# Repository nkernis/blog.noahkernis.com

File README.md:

# blog.noahkernis.com

These are notes on writing posts. 

For usage, see [Hugo](https://gohugo.io/).

## Shortcodes

### Figure and Images

```go
{{< figure src="https://s3.amazonaws.com/media.noahkernis.com/images/life_is_weird.gif" alt="description of image" caption="[ title ]" >}}
```

### Code

```go
{{< code language="javascript" title="code code code" line-numbers="true">}}
function carl() {
	console.log("carla")
}
{{< /code >}}
```

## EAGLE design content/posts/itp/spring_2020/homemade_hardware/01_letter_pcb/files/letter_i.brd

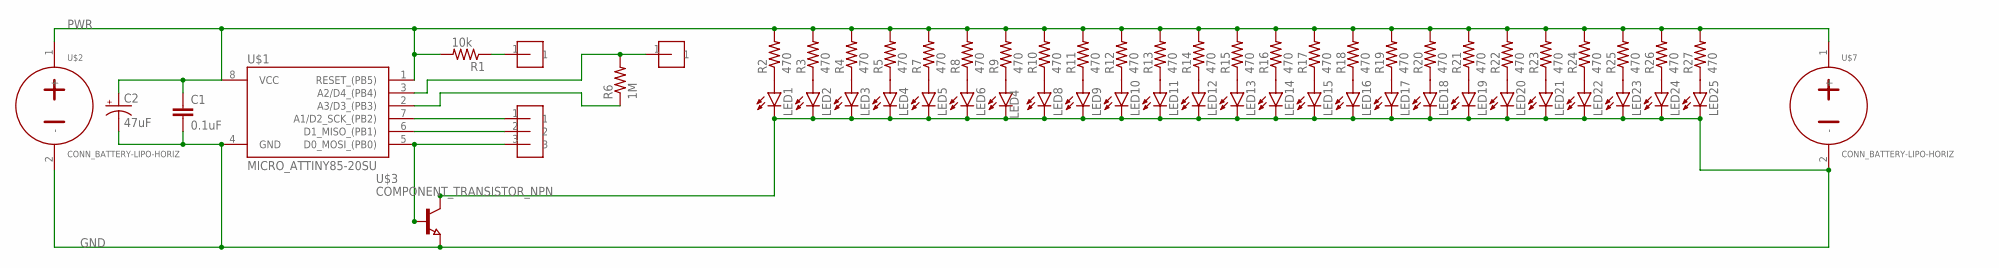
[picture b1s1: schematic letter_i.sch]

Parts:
C1: 0.1uF; 0805
C2: 47uF; CAP_RADIAL_CAN_10MM
LED1, LED2, LED3, LED4, LED5, LED6, LED7, LED8, LED9, LED10, LED11, LED12, LED13, LED14, LED15, LED16, LED17, LED18, LED19, LED20, LED21, LED22, LED23, LED24, LED25: LED-0805; CHIP-LED0805
R1: 10k; 0805
R2, R3, R4, R5, R7, R8, R9, R10, R11, R12, R13, R14, R15, R16, R17, R18, R19, R20, R21, R22, R23, R24, R25, R26, R27: 470; 0805
R6: 1M; 0805
U$1: MICRO_ATTINY85-20SU; SOIC8
U$2, U$7: CONN_BATTERY-LIPO-HORIZ; JST-PH-2-SMT-RA
U$3: COMPONENT_TRANSISTOR_NPN; SOT23
U$4, U$5: HEADER-1-TESTPOINT; TESTPOINT-1
U$6: HEADER-3-TESTPOINT; TESTPOINT-3

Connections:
GND: C1.2, C2.-, LED1.C, LED2.C, LED3.C, LED4.C, LED5.C, LED6.C, LED7.C, LED8.C, LED9.C, LED10.C, LED11.C, LED12.C, LED13.C, LED14.C, LED15.C, LED16.C, LED17.C, LED18.C, LED19.C, LED20.C, LED21.C, LED22.C, LED23.C, LED24.C, LED25.C, U$1.4 (GND), U$2.2 (-), U$3.2 (E), U$3.3 (C), U$7.2 (-)
unnamed: LED1.A, R2.1
unnamed: LED2.A, R3.1
unnamed: LED3.A, R4.1
unnamed: U$1.5 (D0_MOSI_(PB0)), U$3.1 (B), U$6.3
unnamed: LED4.A, R5.1
unnamed: LED5.A, R7.1
unnamed: LED6.A, R8.1
unnamed: R6.2, U$1.3 (A2/D4_(PB4)), U$4.1
unnamed: R1.1, U$5.1
unnamed: LED7.A, R9.1
unnamed: U$1.7 (A1/D2_SCK_(PB2)), U$6.1
unnamed: U$1.6 (D1_MISO_(PB1)), U$6.2
unnamed: LED8.A, R10.1
unnamed: R6.1, U$1.2 (A3/D3_(PB3))
unnamed: LED9.A, R11.1
unnamed: LED10.A, R12.1
unnamed: LED11.A, R13.1
unnamed: LED12.A, R14.1
unnamed: LED13.A, R15.1
unnamed: LED14.A, R16.1
unnamed: LED15.A, R17.1
unnamed: LED16.A, R18.1
unnamed: LED17.A, R19.1
unnamed: LED18.A, R20.1
unnamed: LED19.A, R21.1
unnamed: LED20.A, R22.1
unnamed: LED21.A, R23.1
unnamed: LED22.A, R24.1
unnamed: LED23.A, R25.1
unnamed: LED24.A, R26.1
unnamed: LED25.A, R27.1
PWR: C1.1, C2.+, R1.2, R2.2, R3.2, R4.2, R5.2, R7.2, R8.2, R9.2, R10.2, R11.2, R12.2, R13.2, R14.2, R15.2, R16.2, R17.2, R18.2, R19.2, R20.2, R21.2, R22.2, R23.2, R24.2, R25.2, R26.2, R27.2, U$1.1 (RESET_(PB5)), U$1.8 (VCC), U$2.1 (+), U$7.1 (+)

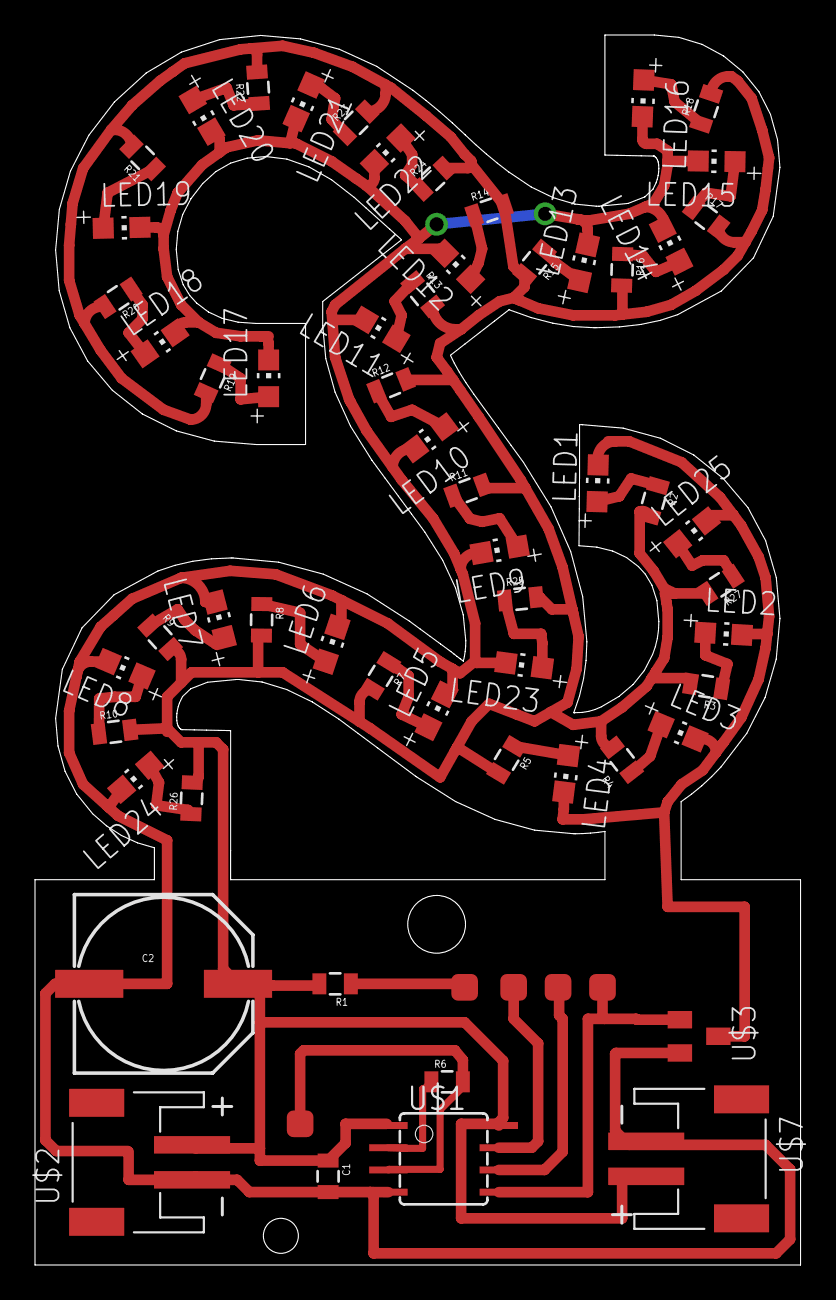
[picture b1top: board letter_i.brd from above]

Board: 2 copper layers, 43.7 x 70.3 mm, 61 parts (0 on the bottom side), 33 nets.

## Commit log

2019-06-23 intitial commit
2019-08-27 commit on new comp
2019-08-30 Base config done
2019-08-30 shortcode for listing all tags on archive page
2019-08-31 changed green color and bg color to custom
2019-08-31 added content to about page
2019-08-31 added subtitle to main page. also removed tag list appearing again on posts
2019-08-31 cover images now support alt text - via 'alt' Param
2019-08-31 changed to pink. made all colors better for contrast
2019-08-31 page is now full width
2019-08-31 set up gdpr - built in hugo
2019-08-31 save
2019-08-31 change for deply
2019-08-31 added netlify.toml
2019-08-31 Removed submodule
2019-08-31 theme back
2019-08-31 publci version
2019-08-31 new bg color for better contrast with pink
2019-08-31 clicking theme makers name opens link in new tab
2019-08-31 new intro for archive page
2019-09-01 new colors
2019-09-01 stule fix
2019-09-01 reset gpsh
2019-09-01 reset
2019-09-01 reset - again
2019-09-01 reset base url
2019-09-01 fix for copy button
2019-09-01 ready for testing
2019-09-01 package-lock
2019-09-01 removed sample site
2019-09-01 theme rebuilt the proper way
2019-09-01 tweaked first post...
2019-09-01 fixed font colors for code highlighting
2019-09-01 larger 'read more' font size. posts list is full page width.
2019-09-02 non accessible font sizes made bigger
2019-09-02 fix list not being full width
2019-09-02 new figure caption css
2019-09-02 reorganized content dir
2019-09-02 its centered - apparently better for reading - all the other sites are doing it sorta thing...
2019-09-02 new subtitle
2019-09-03 new feature - taglines are radnom on home page
2019-09-03 correct id name for taglines tag
2019-09-03 fix script tag for custom taglines
2019-09-03 this work?
2019-09-03 this work 1
2019-09-03 this work 2
2019-09-03 working random taglines
2019-09-03 more taglines
2019-09-03 spelling...
2019-09-03 better buttons
2019-09-03 fixed first post
2019-09-04 new tmp post
2019-09-05 index pages for classes, taglines on all list pages
2019-09-05 syntax fix
2019-09-05 better button sizes
2019-09-05 added missed files
2019-09-09 gif partial
2019-09-09 images for post
2019-09-09 way better location for images
2019-09-09 cover images can now use relative path
2019-09-09 smaller maz size for images (70% width)
2019-09-10 post done
2019-09-10 new gif
2019-09-10 gif is better size
2019-09-10 removed
2019-09-10 added back
2019-09-10 fixed
2019-09-10 added gif
2019-09-10 removed test file - applications
2019-09-11 design analysis post
2019-09-11 fix to articles
2019-09-18 3 blogs (2 are drafts). sizing fix to figure
2019-09-18 pcomp post 1, 5/6 done (weird fraction - right?...)
2019-09-18 tagline for post
2019-09-18 images for expressive words post
2019-09-18 tagline
2019-09-21 expressive words post done
2019-09-25 minimal vis lang post
2019-09-25 more photos
2019-09-25 fixed photos
2019-10-02 winter show poster
2019-10-02 no .MOV
2019-10-02 .gitignore change
2019-10-09 images for my brand
2019-10-09 finsihed post
2019-10-09 new logo
2019-10-09 v2 poster
2019-10-09 alt for logo
2019-10-13 logo fix
2019-10-16 Etch A Sketch
2019-10-16 photos
2019-10-16 title fix
2019-10-16 mem boxes done
2019-10-16 all fab posts created
2019-10-16 templated files
2019-10-17 more posts... fab
2019-10-17 concrete
2019-10-17 rest of concrete photos - gifs to com,e
2019-10-18 logo0 fix
2019-10-18 fix for logo fix...
2019-10-18 another tyr
2019-10-18 smaller photos
2019-11-20 post on materials
2019-11-20 spellcheck...
2019-11-20 new pm page for pcomp final
2019-11-20 iframes yo
2019-11-20 syntax
2019-11-20 chnage color
2019-12-12 self reinforcement
2019-12-12 img in right place
2019-12-19 getting photos up
2019-12-19 path for img
2019-12-19 here are photos...
2019-12-19 ordered photoes
2019-12-19 organized document order
2019-12-19 svae
2020-02-03 spring_2020 added
2020-02-03 place holder posts for spring 2020
2020-02-05 research for meaningful intxn
2020-02-05 more resources
2020-02-05 test
2020-02-05 test1
2020-02-05 more research
2020-02-14 00_dead_person_switch
2020-02-14 added code
2020-02-14 compressed gif
2020-02-14 post complete
2020-02-14 post complete - formatting
2020-02-18 placed 2020 under itp
2020-02-18 critical objects: *plead for your pills*: added photos
2020-02-18 template has default sections now
2020-02-18 added photo
2020-02-18 align ifram
2020-02-18 align iframe
2020-02-18 code section
2020-02-19 added sketcxh photo
2020-02-19 finished build section
2020-02-19 done
2020-02-19 concept for USB Human Interface Device (HID)
2020-02-19 typo
2020-02-19 added tangible_device
2020-02-19 organizing
2020-02-19 problem statement
2020-02-19 prior art
2020-02-19 publish - not draft
2020-02-19 image
2020-02-19 section name change
2020-02-21 hmhw 01
2020-02-21 hmhw 01 - files
2020-02-21 hmhw 01 - file location fix
2020-02-22 hmhw 01 - new files
2020-02-22 hmhw 01 - desc
2020-02-22 hmhw 01 - +text
2020-02-22 hmhw 01 - new title
2020-02-26 user flow - dmi
2020-02-26 rotated photo - dmi
2020-02-26 more on thinking - dmi
2020-02-26 next steps - dmi
2020-02-26 title update - dmi
2020-03-13 final project - hh
2020-03-30 crit obj - spray to play
2020-03-30 crit obj - rotated photos
2020-03-30 crit obj - edits
2020-03-30 crit obj - more images
2020-04-03 hh - breadboard of project
2020-04-06 cc - tcp
2020-04-06 cc - more tcp
2020-04-07 co - plead for pill;s
2020-04-13 cc - final proposal
2020-07-18 Bump lodash from 4.17.15 to 4.17.19 in /themes/terminal
    Bumps [lodash](https://github.com/lodash/lodash) from 4.17.15 to 4.17.19.
    - [Release notes](https://github.com/lodash/lodash/releases)
    - [Commits](https://github.com/lodash/lodash/compare/4.17.15...4.17.19)
2020-07-31 Bump elliptic from 6.5.0 to 6.5.3 in /themes/terminal
    Bumps [elliptic](https://github.com/indutny/elliptic) from 6.5.0 to 6.5.3.
    - [Release notes](https://github.com/indutny/elliptic/releases)
    - [Commits](https://github.com/indutny/elliptic/compare/v6.5.0...v6.5.3)
2020-08-29 fall 2020 classes
2020-08-29 new classes
2020-08-29 new classes - working
2020-08-29 new classes tmp posts
2020-08-30 custom figure and image shortcodes
2020-08-30 custom _defaults and partials
2020-08-30 custom static
2020-08-30 removed edited theme
2020-08-30 added terminal them as git module
2020-08-30 move source to assates
2020-08-30 new color
2020-08-30 new color applied everywhere
2020-08-31 new font sizing
2020-08-31 new logo and formatting for joke
2020-08-31 ready to merge with master
2020-08-31 fixing theme issue
2020-08-31 deploy v2 of site
2020-08-31 added package.json
2020-08-31 fix for menu
2020-08-31 menu and logo fix for mobile
2020-08-31 formatting for footer
2020-08-31 added babel to package.json
2020-08-31 404 fix
2020-08-31 new 404
2020-08-31 footer - hugo 2x underline
2020-08-31 menu fixed for mobile
2020-08-31 fixed bullet spacing
2020-08-31 code size larger
2020-09-01 syntax hightlighting for code updated
2020-09-01 custom shortcode for code
2020-09-11 poem generator
2020-09-11 poem generator updated. also add css to make code lines correct font size
2020-09-11 poem generator - spelling
2020-09-11 underline for links
2020-09-11 embed github gist
2020-09-17 temp post for digi fab
2020-09-23 time - start of post for sketch 1
2020-09-24 time - images for sketch 1
2020-09-24 time - update text for sketch 1
2020-09-29 rwet - digital cutup poem
2020-09-30 time - midterm proposal
2020-09-30 time - sketch1
2020-10-01 digi fab - scale and context
2020-10-01 digi fab - scale and context - updated sizes
2020-10-01 digi fab - scale and context - spelling and such
2020-10-07 time -sketch2
2020-10-08 digi fab - update to proposal post
2020-10-08 digi fab - fix for image ref
2020-10-08 digi fab - fix for a ref
2020-10-08 digi fab - progress update 1
2020-10-08 digi fab - progress update 1, more steps
2020-10-08 digi fab - progress update 1 - images
2020-10-08 digi fab - progress update 1 - syntax
2020-10-08 digi fab - progress update 1 - correct image ref
2020-10-13 rwet - text for genre stufy
2020-10-16 rwet - genre study gist
2020-10-29 rwet - ass. 4
2020-10-29 rwet - correct ref link
2020-10-29 rwet - edited writing
2020-11-01 time - final
2020-11-13 rwet - #5
2020-11-25 time - final project idea
2020-11-25 time - final project idea - update 1
2020-11-25 time - final project idea - fix
2020-11-25 time - final project idea - update 1 (for real...)
2020-11-25 time - **
2020-12-08 rwet - final
2020-12-08 rwet - final, missing photo
2020-12-08 rwet - final, nixon v kennedy was in 60, and first were 4 years before that
2020-12-08 rwet - final, spelling
2020-12-08 rwet - final, new pdf
2020-12-09 rwet - final, new pdf v2
2020-12-09 new blog footer
2020-12-09 new blog footer 03
2020-12-09 new blog footer 04
2020-12-09 new blog footer 05
2021-04-01 Bump y18n from 4.0.0 to 4.0.1
    Bumps [y18n](https://github.com/yargs/y18n) from 4.0.0 to 4.0.1.
    - [Release notes](https://github.com/yargs/y18n/releases)
    - [Changelog](https://github.com/yargs/y18n/blob/master/CHANGELOG.md)
    - [Commits](https://github.com/yargs/y18n/commits)
2021-05-11 Bump lodash from 4.17.20 to 4.17.21
    Bumps [lodash](https://github.com/lodash/lodash) from 4.17.20 to 4.17.21.
    - [Release notes](https://github.com/lodash/lodash/releases)
    - [Commits](https://github.com/lodash/lodash/compare/4.17.20...4.17.21)
2021-05-26 Bump browserslist from 4.14.0 to 4.16.5
    Bumps [browserslist](https://github.com/browserslist/browserslist) from 4.14.0 to 4.16.5.
    - [Release notes](https://github.com/browserslist/browserslist/releases)
    - [Changelog](https://github.com/browserslist/browserslist/blob/main/CHANGELOG.md)
    - [Commits](https://github.com/browserslist/browserslist/compare/4.14.0...4.16.5)
2021-06-17 Bump postcss from 7.0.32 to 7.0.36
    Bumps [postcss](https://github.com/postcss/postcss) from 7.0.32 to 7.0.36.
    - [Release notes](https://github.com/postcss/postcss/releases)
    - [Changelog](https://github.com/postcss/postcss/blob/main/CHANGELOG.md)
    - [Commits](https://github.com/postcss/postcss/compare/7.0.32...7.0.36)
    ---
    updated-dependencies:
